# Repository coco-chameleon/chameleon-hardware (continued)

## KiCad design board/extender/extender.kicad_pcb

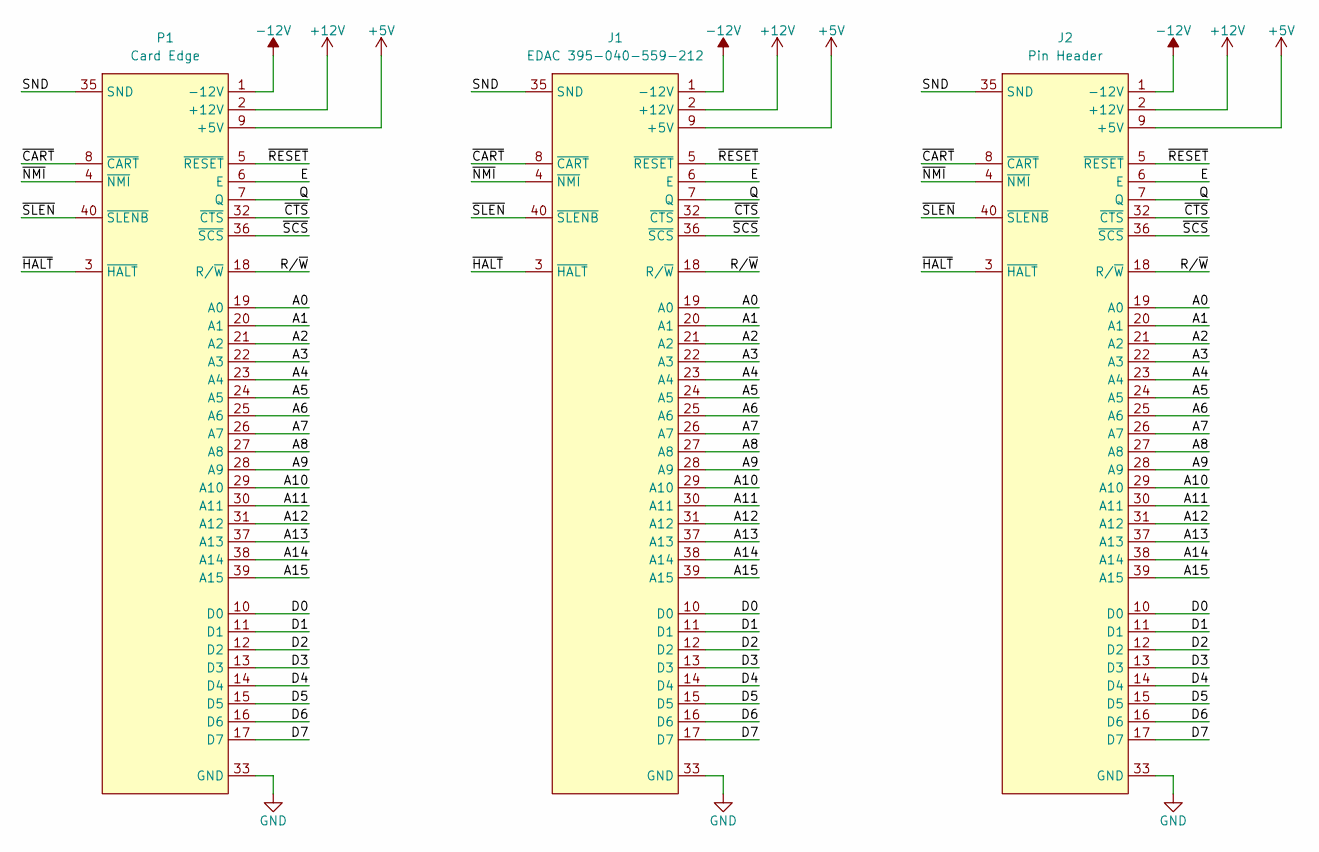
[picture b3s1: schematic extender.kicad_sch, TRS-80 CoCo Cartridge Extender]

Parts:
J1: EDAC 395-040-559-212; EDAC_395-040-559-212
J2: Pin Header; PinHeader_2x20_P2.54mm_Vertical
P1: Card Edge; CoCo_Cart

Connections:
+5V: J1.9 (+5V), J2.9 (+5V), P1.9 (+5V)
+12V: J1.2 (+12V), J2.2 (+12V), P1.2 (+12V)
-12V: J1.1 (-12V), J2.1 (-12V), P1.1 (-12V)
/A0: J1.19 (A0), J2.19 (A0), P1.19 (A0)
/A1: J1.20 (A1), J2.20 (A1), P1.20 (A1)
/A2: J1.21 (A2), J2.21 (A2), P1.21 (A2)
/A3: J1.22 (A3), J2.22 (A3), P1.22 (A3)
/A4: J1.23 (A4), J2.23 (A4), P1.23 (A4)
/A5: J1.24 (A5), J2.24 (A5), P1.24 (A5)
/A6: J1.25 (A6), J2.25 (A6), P1.25 (A6)
/A7: J1.26 (A7), J2.26 (A7), P1.26 (A7)
/A8: J1.27 (A8), J2.27 (A8), P1.27 (A8)
/A9: J1.28 (A9), J2.28 (A9), P1.28 (A9)
/A10: J1.29 (A10), J2.29 (A10), P1.29 (A10)
/A11: J1.30 (A11), J2.30 (A11), P1.30 (A11)
/A12: J1.31 (A12), J2.31 (A12), P1.31 (A12)
/A13: J1.37 (A13), J2.37 (A13), P1.37 (A13)
/A14: J1.38 (A14), J2.38 (A14), P1.38 (A14)
/A15: J1.39 (A15), J2.39 (A15), P1.39 (A15)
/D0: J1.10 (D0), J2.10 (D0), P1.10 (D0)
/D1: J1.11 (D1), J2.11 (D1), P1.11 (D1)
/D2: J1.12 (D2), J2.12 (D2), P1.12 (D2)
/D3: J1.13 (D3), J2.13 (D3), P1.13 (D3)
/D4: J1.14 (D4), J2.14 (D4), P1.14 (D4)
/D5: J1.15 (D5), J2.15 (D5), P1.15 (D5)
/D6: J1.16 (D6), J2.16 (D6), P1.16 (D6)
/D7: J1.17 (D7), J2.17 (D7), P1.17 (D7)
/E: J1.6 (E), J2.6 (E), P1.6 (E)
/Q: J1.7 (Q), J2.7 (Q), P1.7 (Q)
/R/~W: J1.18 (R/~W), J2.18 (R/~W), P1.18 (R/~W)
/SND: J1.35 (SND), J2.35 (SND), P1.35 (SND)
/~CART: J1.8 (~CART), J2.8 (~CART), P1.8 (~CART)
/~CTS: J1.32 (~CTS), J2.32 (~CTS), P1.32 (~CTS)
/~HALT: J1.3 (~HALT), J2.3 (~HALT), P1.3 (~HALT)
/~NMI: J1.4 (~NMI), J2.4 (~NMI), P1.4 (~NMI)
/~RESET: J1.5 (~RESET), J2.5 (~RESET), P1.5 (~RESET)
/~SCS: J1.36 (~SCS), J2.36 (~SCS), P1.36 (~SCS)
/~SLEN: J1.40 (~SLENB), J2.40 (~SLENB), P1.40 (~SLENB)
GND: J1.33 (GND), J1.34 (GND), J2.33 (GND), J2.34 (GND), P1.33 (GND), P1.34 (GND)

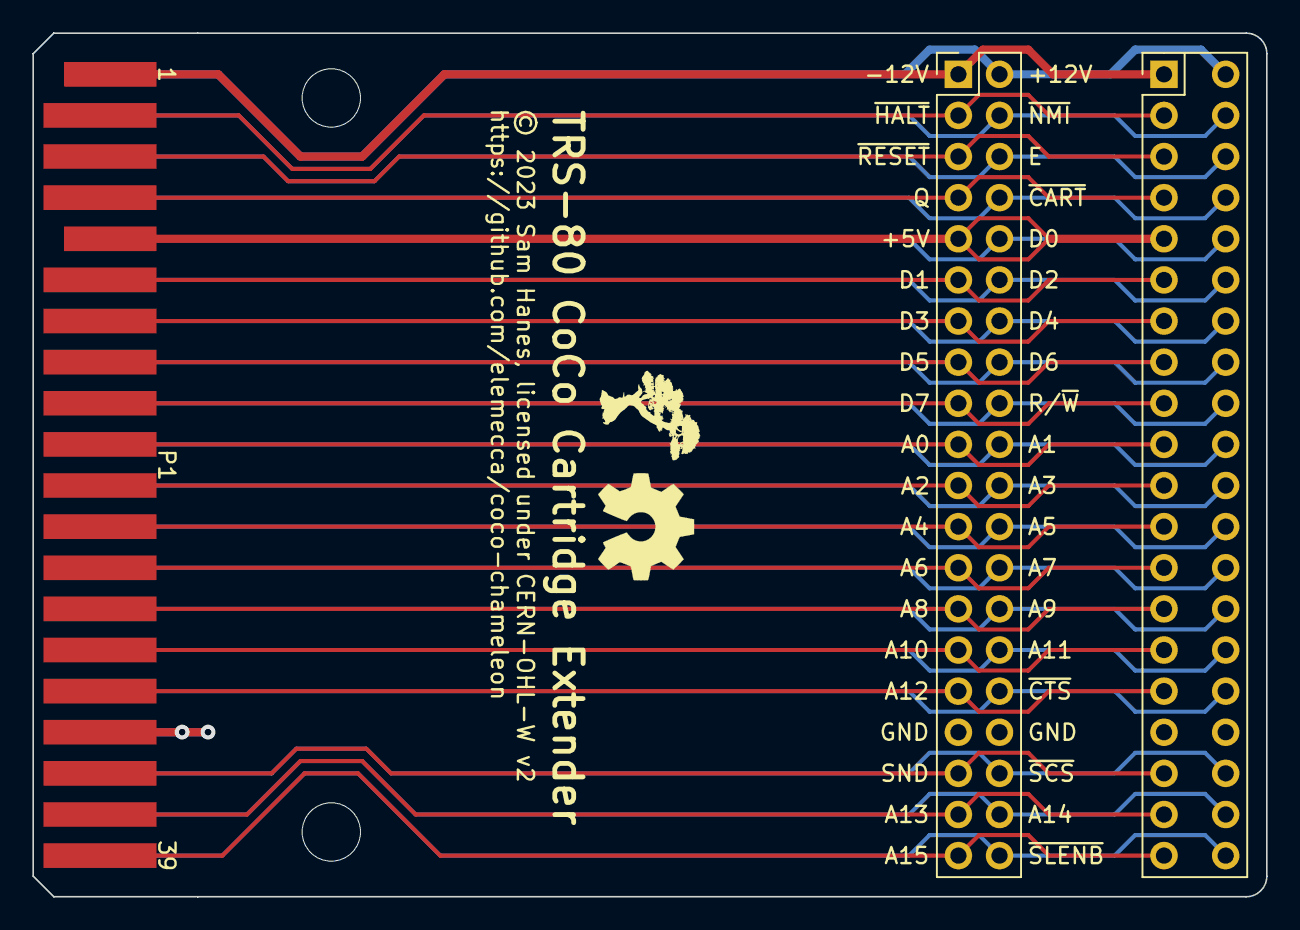
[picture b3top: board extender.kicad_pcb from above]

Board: 4 copper layers, 76.2 x 53.3 mm, 5 parts (0 on the bottom side), 39 nets.

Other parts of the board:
MH1, MH2: CoCo_MountingHole

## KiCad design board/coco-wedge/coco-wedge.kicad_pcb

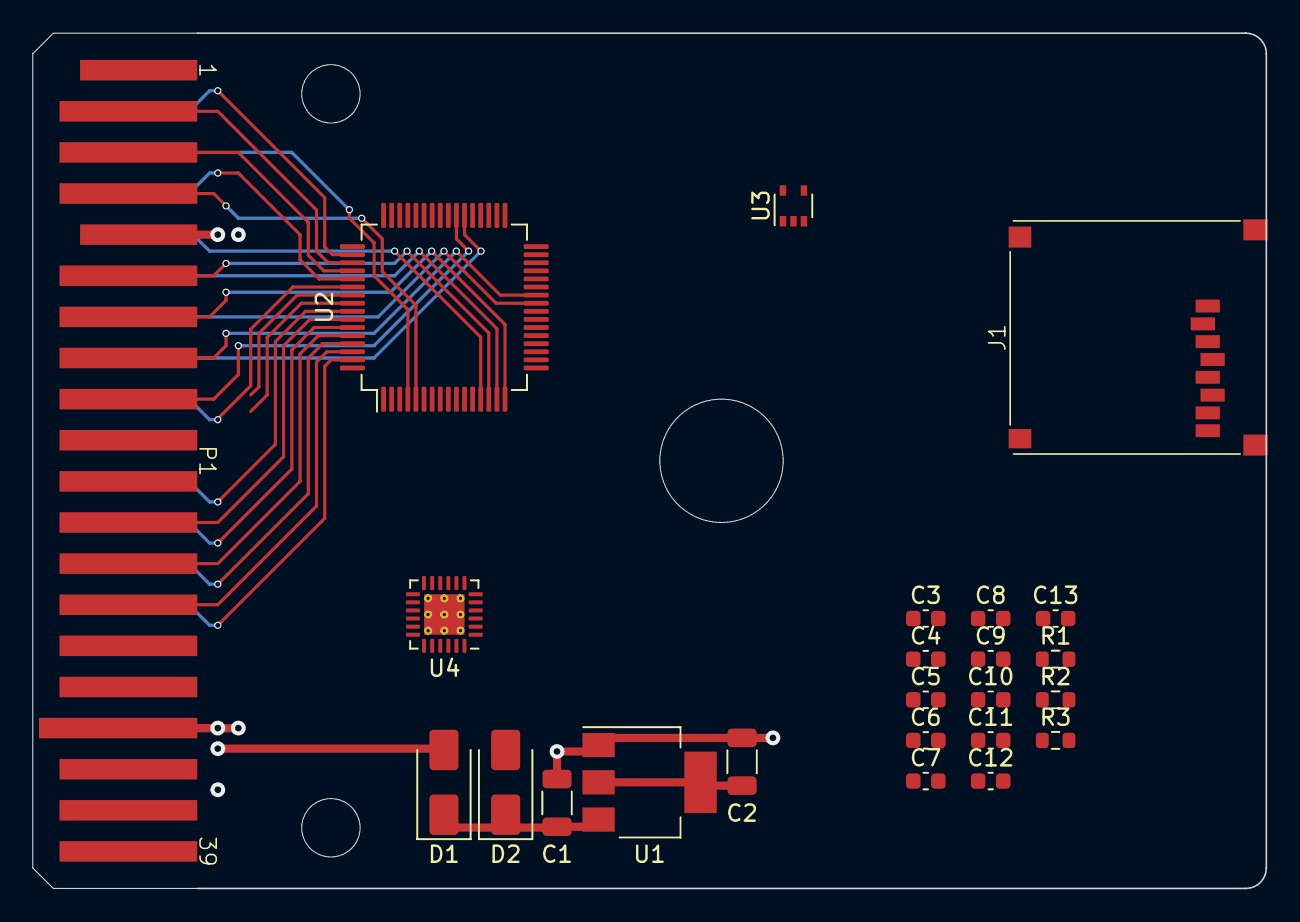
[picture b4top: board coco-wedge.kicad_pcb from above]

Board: 4 copper layers, 76.2 x 52.8 mm, 24 parts (0 on the bottom side), 57 nets.

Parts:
C1, C2: 22u; C_1206_3216Metric
C3, C4: 20p; C_0603_1608Metric
C5, C7, C8, C9, C11, C12: 4u7; C_0603_1608Metric
C6: 100n; C_0603_1608Metric
C10, C13: 1u; C_0603_1608Metric
D1, D2: SS12-AT; D_SMA
J1: Foxconn_WQ21823-DES1-7F
P1: CoCo_Cart
R1, R2, R3: 100k; R_0603_1608Metric
U1: AMS1117-3.3; SOT-223-3_TabPin2
U2: STM32G0B0RETx; LQFP-64_10x10mm_P0.5mm
U3: 74LVC1G07; SOT-353_SC-70-5
U4: NAU8814Y; VQFN-24-1EP_4x4mm_P0.5mm_EP2.5x2.5mm_ThermalVias

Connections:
+3V3: C2.1, C5.1, C6.1, C7.1, C8.1, C9.1, C11.1, J1.4 (VDD), U1.2 (VO), U2.6 (VBAT), U2.7 (VREF+), U2.8 (VDD), U3.5 (VCC), U4.2 (VDDA), U4.4 (VDDC), U4.5 (VDDB)
+5V: D1.2 (A), P1.9 (+5V)
/+5V_IN: C1.1, D1.1 (K), D2.1 (K), U1.3 (VI)
/A0: P1.19 (A0), U2.27 (PB0)
/A1: P1.20 (A1), U2.28 (PB1)
/A2: P1.21 (A2), U2.29 (PB2)
/A3: P1.22 (A3), U2.57 (PB3)
/A4: P1.23 (A4), U2.58 (PB4)
/A5: P1.24 (A5), U2.59 (PB5)
/A6: P1.25 (A6), U2.60 (PB6)
/A7: P1.26 (A7), U2.61 (PB7)
/A8: P1.27 (A8), U2.62 (PB8)
/A9: P1.28 (A9), U2.63 (PB9)
/A10: P1.29 (A10), U2.30 (PB10)
/A11: P1.30 (A11), U2.31 (PB11)
/A12: P1.31 (A12), U2.32 (PB12)
/A13: P1.37 (A13), U2.33 (PB13)
/A14: P1.38 (A14), U2.34 (PB14)
/A15: P1.39 (A15), U2.35 (PB15)
/D0: P1.10 (D0), U2.13 (PC0)
/D1: P1.11 (D1), U2.14 (PC1)
/D2: P1.12 (D2), U2.15 (PC2)
/D3: P1.13 (D3), U2.16 (PC3)
/D4: P1.14 (D4), U2.25 (PC4)
/D5: P1.15 (D5), U2.26 (PC5)
/D6: P1.16 (D6), U2.38 (PC6)
/D7: P1.17 (D7), U2.39 (PC7)
/E: P1.6 (E), U2.4 (PC14)
/I2C_SCL: U2.24 (PA7), U4.13 (SCLK)
/I2C_SDA: U2.23 (PA6), U4.14 (SDIO)
/I2S_BCLK: U2.17 (PA0), U2.18 (PA1), U4.10 (BCLK)
/I2S_FS: U2.21 (PA4), U2.36 (PA8), U4.9 (FS)
/I2S_IN: U2.22 (PA5), U4.7 (ADCOUT)
/I2S_MCLK: U2.37 (PA9/NC), U4.11 (MCLK)
/I2S_OUT: U2.19 (PA2), U4.8 (DACIN)
/OSC_IN: C3.1, U2.10 (PF0)
/OSC_OUT: C4.1, U2.11 (PF1)
/Q: P1.7 (Q), U2.5 (PC15)
/R/~W: P1.18 (R/~W), U2.54 (PD4)
/SD_MISO: J1.7 (DAT0), U2.1 (PC11)
/SD_MOSI: J1.3 (CMD), U2.2 (PC12)
/SD_SCLK: J1.5 (CLK), U2.64 (PC10)
/SD_~CS: J1.2 (DAT3/CD), U2.47 (PA15)
/SND: C10.2, C13.1, P1.35 (SND)
/~BOOT: R1.2, U2.20 (PA3), U3.2
/~CART: P1.8 (~CART), U2.53 (PD3)
/~CTS: P1.32 (~CTS), U2.55 (PD5)
/~HALT: P1.3 (~HALT), U2.51 (PD1)
/~NMI: P1.4 (~NMI), U2.50 (PD0)
/~RESET: P1.5 (~RESET), U2.52 (PD2), U3.4
/~SCS: P1.36 (~SCS), U2.56 (PD6)
/~SLEN: P1.40 (~SLENB), U2.40 (PD8)
GND: C1.2, C2.2, C3.2, C4.2, C5.2, C6.2, C7.2, C8.2, C9.2, C11.2, C12.2, J1.6 (VSS), J1.9 (DET_B), J1.11 (SHIELD), P1.33 (GND), P1.34 (GND), R2.2, U1.1 (GND), U2.9 (VSS), U3.3 (GND), U4.3 (VSSA), U4.6 (VSSD), U4.12 (~CS/GPIO), U4.15 (MODE), U4.18 (VSSPK), U4.25 (VSSA)
unnamed: C13.2, R3.2, U4.21 (AUX)
unnamed: R3.1, U4.1 (MICBIAS)
unnamed: C10.1, R2.1, U4.16 (MOUT)
unnamed: C12.1, U4.22 (VREF)

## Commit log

2023-11-28 Start with a partially-designed board.
2023-11-29 Add most of the audio system, do some routing.
2023-11-29 Rename KiCAD project.
2023-11-29 Update schematic info block and add a README.
2023-11-30 Place and route MCU power and crystal.
2023-12-02 Choose parts for everything plus more routing.
2023-12-05 Update footprint positions to match JLCPCB.
2023-12-06 Rip up and try routing as 2 layer.
2023-12-06 Adjust layout based on an actual Tandy cartridge.
2023-12-07 Another attempt at routing.
2023-12-12 Move CoCo footprints up to project.
2023-12-13 Add cartridge extender board.
2023-12-14 More routing.
2023-12-14 Update boot switches to support MultiPak.
2023-12-14 Add missing LCSC numbers.
2023-12-14 Add JLC tooling holes.
2023-12-15 Move pin assignments around to accomodate new switches.
2023-12-20 Switch to cheaper SD card socket, more routing.
2023-12-20 Fully route the card-edge connector.
2023-12-20 Route power for the main ICs.
2023-12-21 Route everything else.
2023-12-21 Misc board cleanup.
2023-12-22 Final cleanup for first cartridge prototype.
2023-12-22 Change extender board to 4-layer.
2024-02-19 Start firmware with embassy-rs and a blinkenlight.
2024-02-22 Use defmt for debug logging.
2024-03-02 Update KiCad projects to v8.
2024-03-03 Sketch out a redesign to use an RP2040.
2024-05-18 Remove STM32 Rust firmware.
2024-05-18 Start updating board to use ESP32-S3.
2024-05-23 Add basic esp-idf project for testing boot times.
2024-05-27 Design and mostly route level shifters.
2024-05-27 Fully route 5V signals.
2024-05-27 Attach control bus to MCU.
2024-06-19 More bus routing.
2024-06-20 Re-route CoCo bus with all 74-245s.
2024-06-20 Remove firmware (moved to its own repo).
2024-06-22 Route more peripherals.
2024-06-25 Add a bunch of USB stuff.
2024-06-30 Finish USB power management.
2024-07-06 Add 32 kHz crystal.
2024-07-10 Start designing cartridge case.
2024-07-10 Add screw posts to enclosure.
2024-07-10 Add bottom shell to enclosure.
2024-07-11 Re-model enclosure screw posts.
2024-07-11 Add shutter pocket to enclosure.
2024-08-06 Start re-modelling the enclosure.
2024-08-06 Fix direction of top case lip.
2024-08-06 Model bottom case.
2024-08-06 Remove old enclosure model.
2024-08-06 Rename new enclosure model.
2024-08-08 Add support ribs to top case and fix shutter clearance.
2024-08-08 Add inner fillets back to top shell.
2024-08-09 Re-model shell to fix fillets.
2024-08-11 Add modelled printing support for top case.
2024-09-06 Add a CR2016 battery holder.
2024-09-19 Reroute around the battery holder.
2024-11-14 Roll back adding CR2016 battery.
2024-11-26 Start working on Li-Poly battery.
2024-12-20 Add support block for top case, upgrade to FC 1.0.
2024-12-22 Add light pipe and fill for arrow.
2025-01-06 Add modeled support for sticker relief.
2025-01-06 Roll back adding Li-Poly battery.
    This reverts commit 081752ba55a88da4e16a76dc68d1f4d967b2094e.
2025-01-27 Add clip recesses to top shell.
2025-01-27 Move USB connector outward 1mm.
2025-01-27 Remove watch crystal and audio DAC.
    These can be implemented later; they're not needed
    for a first-gen prototype to determine whether the
    ESP32-S3 will even be able to bit-bang the bus.
2025-01-28 Adjust clearance on insets and clips.
2025-01-29 Re-model shutter pocket.
2025-01-30 Start modelling shutter.
2025-01-31 Model clips on bottom shell.
2025-02-18 Start trying to print the bottom case.
2025-02-18 Start adjusting select logic for testing.
2025-07-20 Finish adding solder links for configuration.
2025-07-21 Ensure all parts are available from DigiKey and JLCPCB.
    This switches the symbols and footprints to the more widely available
    parts sourced from DigiKey. Parts also have an LCSC catalog number,
    which may be the same part or a cheaper compatible clone.
2025-07-22 Remove USB host bulk capacitor.
    I'm reasonably certain the bulk capacitor referred to by the USB 2.0
    spec is only actually required for multi-port hubs.
2025-07-22 Fix issues with ESP32-S3-WROOM-1U library footprint.
2025-08-13 Bump board version.
2026-02-08 Start working on RP3250 layout.
2026-02-11 Route most of the RP2350.
2026-02-12 Finish routing RP2350.
2026-02-18 Add RTC and start adding DAC.
2026-02-27 Start playing with a test harness board.
